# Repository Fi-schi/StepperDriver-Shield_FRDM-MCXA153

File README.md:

# StepperDriver-Shield_FRDM-MCXA153

This is a shield for the FRDM-MCXA153 microcontroller, developed as part of my mechatronic course project at the Hochschule Wismar, University of Applied Sciences: Technology, Economy and Design.

The board acts as a carrier for the TMC-2209 stepper drivers and allows up to four stepper motors to be controlled simultaneously.

It is designed for 24V operation and has three freely programmable buttons, connections for four limit switches and a manual stepper driver enable circuit.
In addition, by soldering a DC-DC converter to the microcontroller, it is possible to supply 24V through the shield.

# Parts for the shield

| Qty. | Part          | Size   | Links |
|------|:-------------:|:------:|:------|
|  7x  |     0.1µF     | 0805   |  |
|  4x  |    100µF/35V  | 6.3mm  | https://www.mouser.de/ProductDetail/661-EMZR350ARA101MF6 |
|  13x |    10K&Omega; | 0805   |  |
|  4x  |    100&Omega; | 0805   |  |
|  1x  |    1K&Omega;  | 0805   |  |
|  4x  |TVS-Diode 3.3V | 0603   | https://www.mouser.de/ProductDetail/652-CG0603MLC-3.3LE |
|  1x  |   74LVC2G00   |TSSOP-8 | https://www.mouser.de/ProductDetail/771-LVC2G00DP125 |
|  1x  |SN74LXC2T45-Q1 | 	VSSOP | https://www.mouser.de/ProductDetail/595-74LXC2T45QDCURQ1 |
|  1x  |    WS2812B    |        |  | 
|  5x  |Tactile Switch | 6x6mm  | https://www.mouser.de/ProductDetail/710-430133050816 |
|  4x  | 1x02 JST_XH   | 2,54mm |  |
|  4x  | 1x04 JST_XH   | 2,54mm |  |
|  1x  | 1x02 PinHeader| 2,54mm |  |
|  8x  | 1x03 PinHeader| 2,54mm |  |
|  9x  | Pin Header Jumper | 2,54mm |  |
|  1x  | AMASS XT60PW-M|        |  |
|  1x  | 2x06 PinHeader (SSW-106-23-G-D) | 2,54mm| https://www.samtec.com/de/products/ssw-106-23-g-d |
|  1x  | 2x08 PinHeader (SSW-108-23-G-D) | 2,54mm| https://www.samtec.com/de/products/ssw-108-23-g-d |
|  2x  | 3x10 PinHeader (SSW-110-23-G-D) | 2,54mm| https://www.samtec.com/de/products/ssw-110-23-g-d |
|  4x  | BTT TMC2019 Stepp Stick | |  |

# Parts for the microcontroller external power supply

| Qty. | Part          | Size   | Links |
|------|:-------------:|:------:|:------|
|  1x  | DC/DC to 5v/500mA| SIP-3  | https://www.mouser.de/ProductDetail/919-R-78CK5.0-0.5 |
|  2x  |    1µF/35V  | 0603  |  |

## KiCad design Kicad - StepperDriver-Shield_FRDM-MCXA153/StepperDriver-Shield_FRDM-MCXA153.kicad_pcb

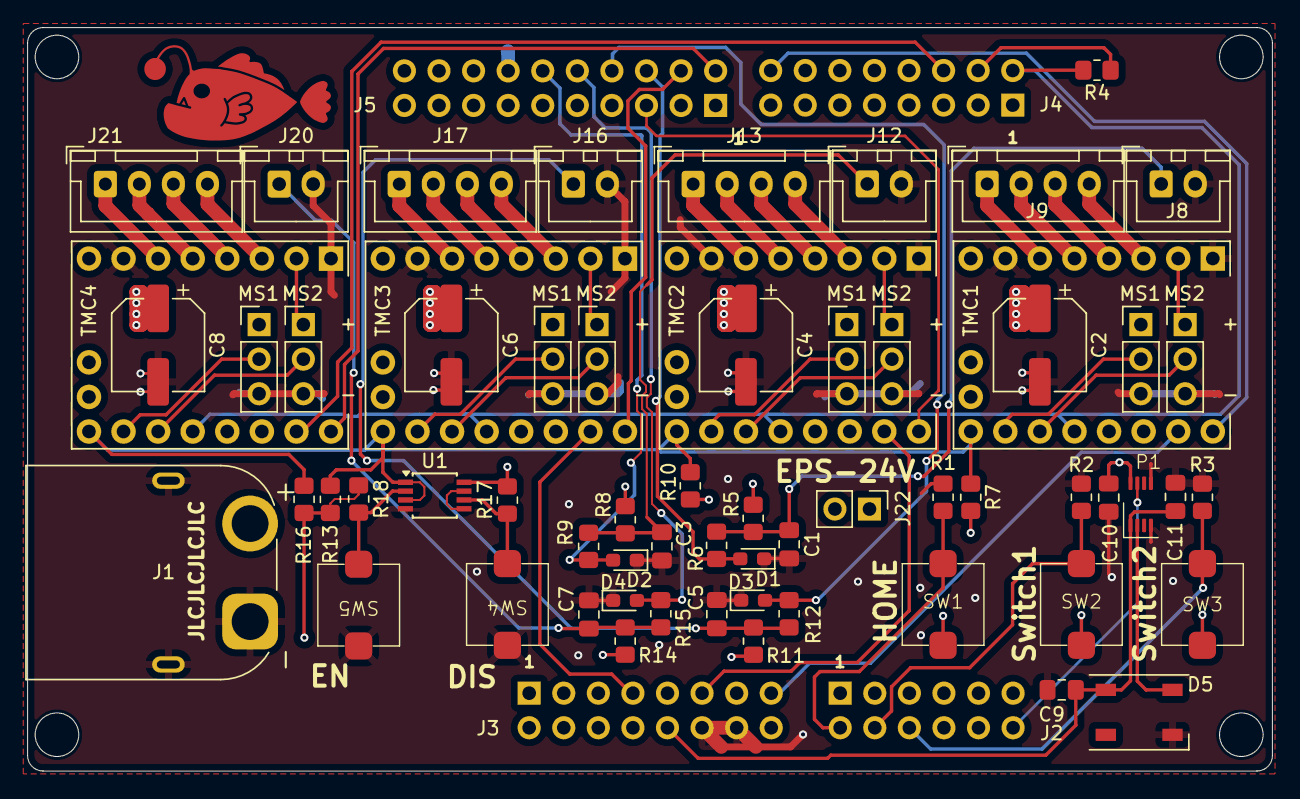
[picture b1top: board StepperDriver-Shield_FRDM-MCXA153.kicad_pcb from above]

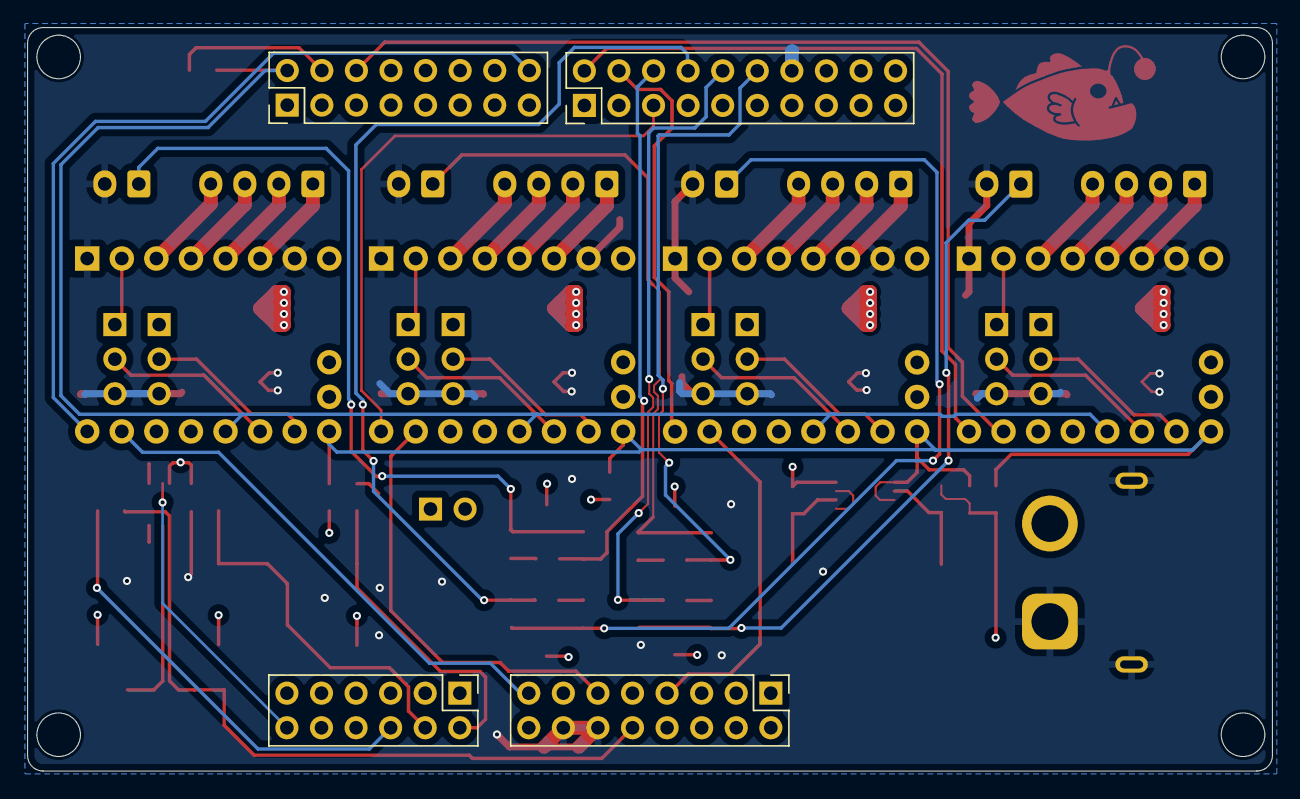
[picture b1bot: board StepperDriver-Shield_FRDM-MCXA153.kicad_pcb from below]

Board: 4 copper layers, 91.4 x 54.6 mm, 72 parts (4 on the bottom side), 56 nets.

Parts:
Blub1: Fischi
C1, C3, C5, C7: 0.1UF; C_0805_2012Metric_Pad1.18x1.45mm_HandSolder
C2, C4, C6, C8: 100UF/35V; CP_Elec_6.3x7.7
C9, C10, C11: 0.1µF; C_0805_2012Metric_Pad1.18x1.45mm_HandSolder
D1, D2, D3, D4: D_TVS; D_0603_1608Metric_Pad1.05x0.95mm_HandSolder
D5: WS2812B; LED_WS2812B_PLCC4_5.0x5.0mm_P3.2mm
H1, H2, H3, H4: Mechanical_MountingHole; MountingHole_3.2mm_M3
J1: Conn_01x02_Socket; AMASS_XT60PW-M
J2: SSQ-106-03-T-D; PinHeader_2x06_P2.54mm_Vertical
J3, J4: SSQ-108-03-T-D; PinHeader_2x08_P2.54mm_Vertical
J5: SSQ-110-03-T-D; PinHeader_2x10_P2.54mm_Vertical
J6, J7, J10, J11, J14, J15, J18, J19: Conn_01x03; PinHeader_1x03_P2.54mm_Vertical
J8, J12, J16, J20: Conn_01x02_Pin; JST_XH_B2B-XH-A_1x02_P2.50mm_Vertical
J9, J13, J17, J21: Conn_01x04_Pin; JST_XH_B4B-XH-A_1x04_P2.50mm_Vertical
J22: Conn_01x02_Socket; PinHeader_1x02_P2.54mm_Vertical
P1: SN74LXC2T45QDCURQ1_; SN74LXC2T45QDCURQ1
R1, R2, R3, R5, R7, R8, R10, R11, R13, R14, R16, R17, R18: 10K; R_0805_2012Metric_Pad1.20x1.40mm_HandSolder
R4: 1K; R_0805_2012Metric_Pad1.20x1.40mm_HandSolder
R6, R9, R12, R15: 100R; R_0805_2012Metric_Pad1.20x1.40mm_HandSolder
SW1: Home; Takt_Schalter_Aliexpress
SW2: SW1; Takt_Schalter_Aliexpress
SW3: SW2; Takt_Schalter_Aliexpress
SW4: DIS; Takt_Schalter_Aliexpress
SW5: EN; Takt_Schalter_Aliexpress
TMC1, TMC2, TMC3, TMC4: TMC2209; Btt_TMC2209_V1.3
U1: 74LVC2G00; TSSOP-8_3x3mm_P0.65mm

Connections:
5v-9v: J3.16, J22.1
/EN_Logic/ENABLE: U1.5, U1.7
/P1-4/UART2-RXD: J4.2, R4.2, TMC1.14 (RX), TMC2.14 (RX), TMC3.14 (RX), TMC4.14 (RX)
/P1-5/UART2-TXD: J4.4, R4.1
/P1-10/ADC0-A8: J2.2, R1.1, SW1.1
/P1-12/ADC0-A10: J2.4, R2.1, SW2.1
/P1-13/ADC0-A11: J2.6, R3.1, SW3.1
/P2-3/ADC0-A2: J5.5, TMC2.18 (DIR)
/P2-4/GPIO: J4.6, TMC4.17 (STEP)
/P2-6/CSI1: D1.2 (A2), J5.6, R6.2
/P2-12/SCK1: D2.2 (A2), J5.12, R9.2
/P2-13/SDO1: D3.2 (A2), J5.8, R12.2
/P2-16/SDI1: D4.2 (A2), J5.10, R15.2
/P3-1/GPIO: J4.16, TMC1.18 (DIR)
/P3-6/PWM0-A0: J3.15, TMC1.17 (STEP)
/P3-8/PWM0-A1: J3.11, TMC2.17 (STEP)
/P3-10/PWM0-A2: J3.7, TMC3.17 (STEP)
/P3-14/PWM0-X2: J5.4, TMC3.18 (DIR)
/P3-15/GPIO: J5.2, TMC4.18 (DIR)
/P3-30/ADC0-A13: J2.12, P1.7 (B1)
/TMC_2209_wiring1/A1: J13.2, TMC2.5 (A1)
/TMC_2209_wiring1/A2: J13.1, TMC2.6 (A2)
/TMC_2209_wiring1/B1: J13.3, TMC2.4 (B1)
/TMC_2209_wiring1/B2: J13.4, TMC2.3 (B2)
/TMC_2209_wiring1/MS1: J11.2, TMC2.12 (MS1)
/TMC_2209_wiring1/MS2: J10.2, TMC2.13 (MS2)
/TMC_2209_wiring2/A1: J17.2, TMC3.5 (A1)
/TMC_2209_wiring2/A2: J17.1, TMC3.6 (A2)
/TMC_2209_wiring2/B1: J17.3, TMC3.4 (B1)
/TMC_2209_wiring2/B2: J17.4, TMC3.3 (B2)
/TMC_2209_wiring2/MS1: J15.2, TMC3.12 (MS1)
/TMC_2209_wiring2/MS2: J14.2, TMC3.13 (MS2)
/TMC_2209_wiring3/A1: J21.2, TMC4.5 (A1)
/TMC_2209_wiring3/A2: J21.1, TMC4.6 (A2)
/TMC_2209_wiring3/B1: J21.3, TMC4.4 (B1)
/TMC_2209_wiring3/B2: J21.4, TMC4.3 (B2)
/TMC_2209_wiring3/MS1: J19.2, TMC4.12 (MS1)
/TMC_2209_wiring3/MS2: J18.2, TMC4.13 (MS2)
/TMC_2209_wiring/A1: J9.2, TMC1.5 (A1)
/TMC_2209_wiring/A2: J9.1, TMC1.6 (A2)
/TMC_2209_wiring/B1: J9.3, TMC1.4 (B1)
/TMC_2209_wiring/B2: J9.4, TMC1.3 (B2)
/TMC_2209_wiring/MS1: J7.2, TMC1.12 (MS1)
/TMC_2209_wiring/MS2: J6.2, TMC1.13 (MS2)
//ENABLE: R7.1, R10.1, R13.1, R16.1, TMC1.11 (/EN), TMC2.11 (/EN), TMC3.11 (/EN), TMC4.11 (/EN), U1.1, U1.3
GND: C1.2, C2.2, C3.2, C4.2, C5.2, C6.2, C7.2, C8.2, C9.1, C10.1, C11.2, D1.1 (A1), D2.1 (A1), D3.1 (A1), D4.1 (A1), D5.3 (VSS), J1.1, J3.12, J3.14, J5.14, J6.3, J7.3, J8.2, J10.3, J11.3, J12.2, J14.3, J15.3, J16.2, J18.3, J19.3, J20.2, P1.4 (GND), P1.5 (DIR), R1.2, R2.2, R3.2, SW4.1, SW5.1, TMC1.1 (GND), TMC1.7 (GND), TMC2.1 (GND), TMC2.7 (GND), TMC3.1 (GND), TMC3.7 (GND), TMC4.1 (GND), TMC4.7 (GND), U1.4 (GND)
unnamed: D5.4 (DIN), P1.2 (A1)
unnamed: C1.1, J8.1, R5.1, R6.1
unnamed: C3.1, J12.1, R8.1, R9.1
unnamed: C5.1, J16.1, R11.1, R12.1
unnamed: C7.1, J20.1, R14.1, R15.1
unnamed: R17.2, SW4.2, U1.6
unnamed: R18.2, SW5.2, U1.2
SYS-5V: C9.2, C11.1, D5.1 (VDD), J3.10, P1.1 (VCC_A)
Vcc_Logic: C10.2, J3.8, J6.1, J7.1, J10.1, J11.1, J14.1, J15.1, J18.1, J19.1, P1.8 (VCC_B), R5.2, R7.2, R8.2, R10.2, R11.2, R13.2, R14.2, R16.2, R17.1, R18.1, SW1.2, SW2.2, SW3.2, TMC1.2 (V_IO), TMC2.2 (V_IO), TMC3.2 (V_IO), TMC4.2 (V_IO), U1.8 (VCC)
Vcc_Motor: C2.1, C4.1, C6.1, C8.1, J1.2, J22.2, TMC1.8 (VS), TMC2.8 (VS), TMC3.8 (VS), TMC4.8 (VS)

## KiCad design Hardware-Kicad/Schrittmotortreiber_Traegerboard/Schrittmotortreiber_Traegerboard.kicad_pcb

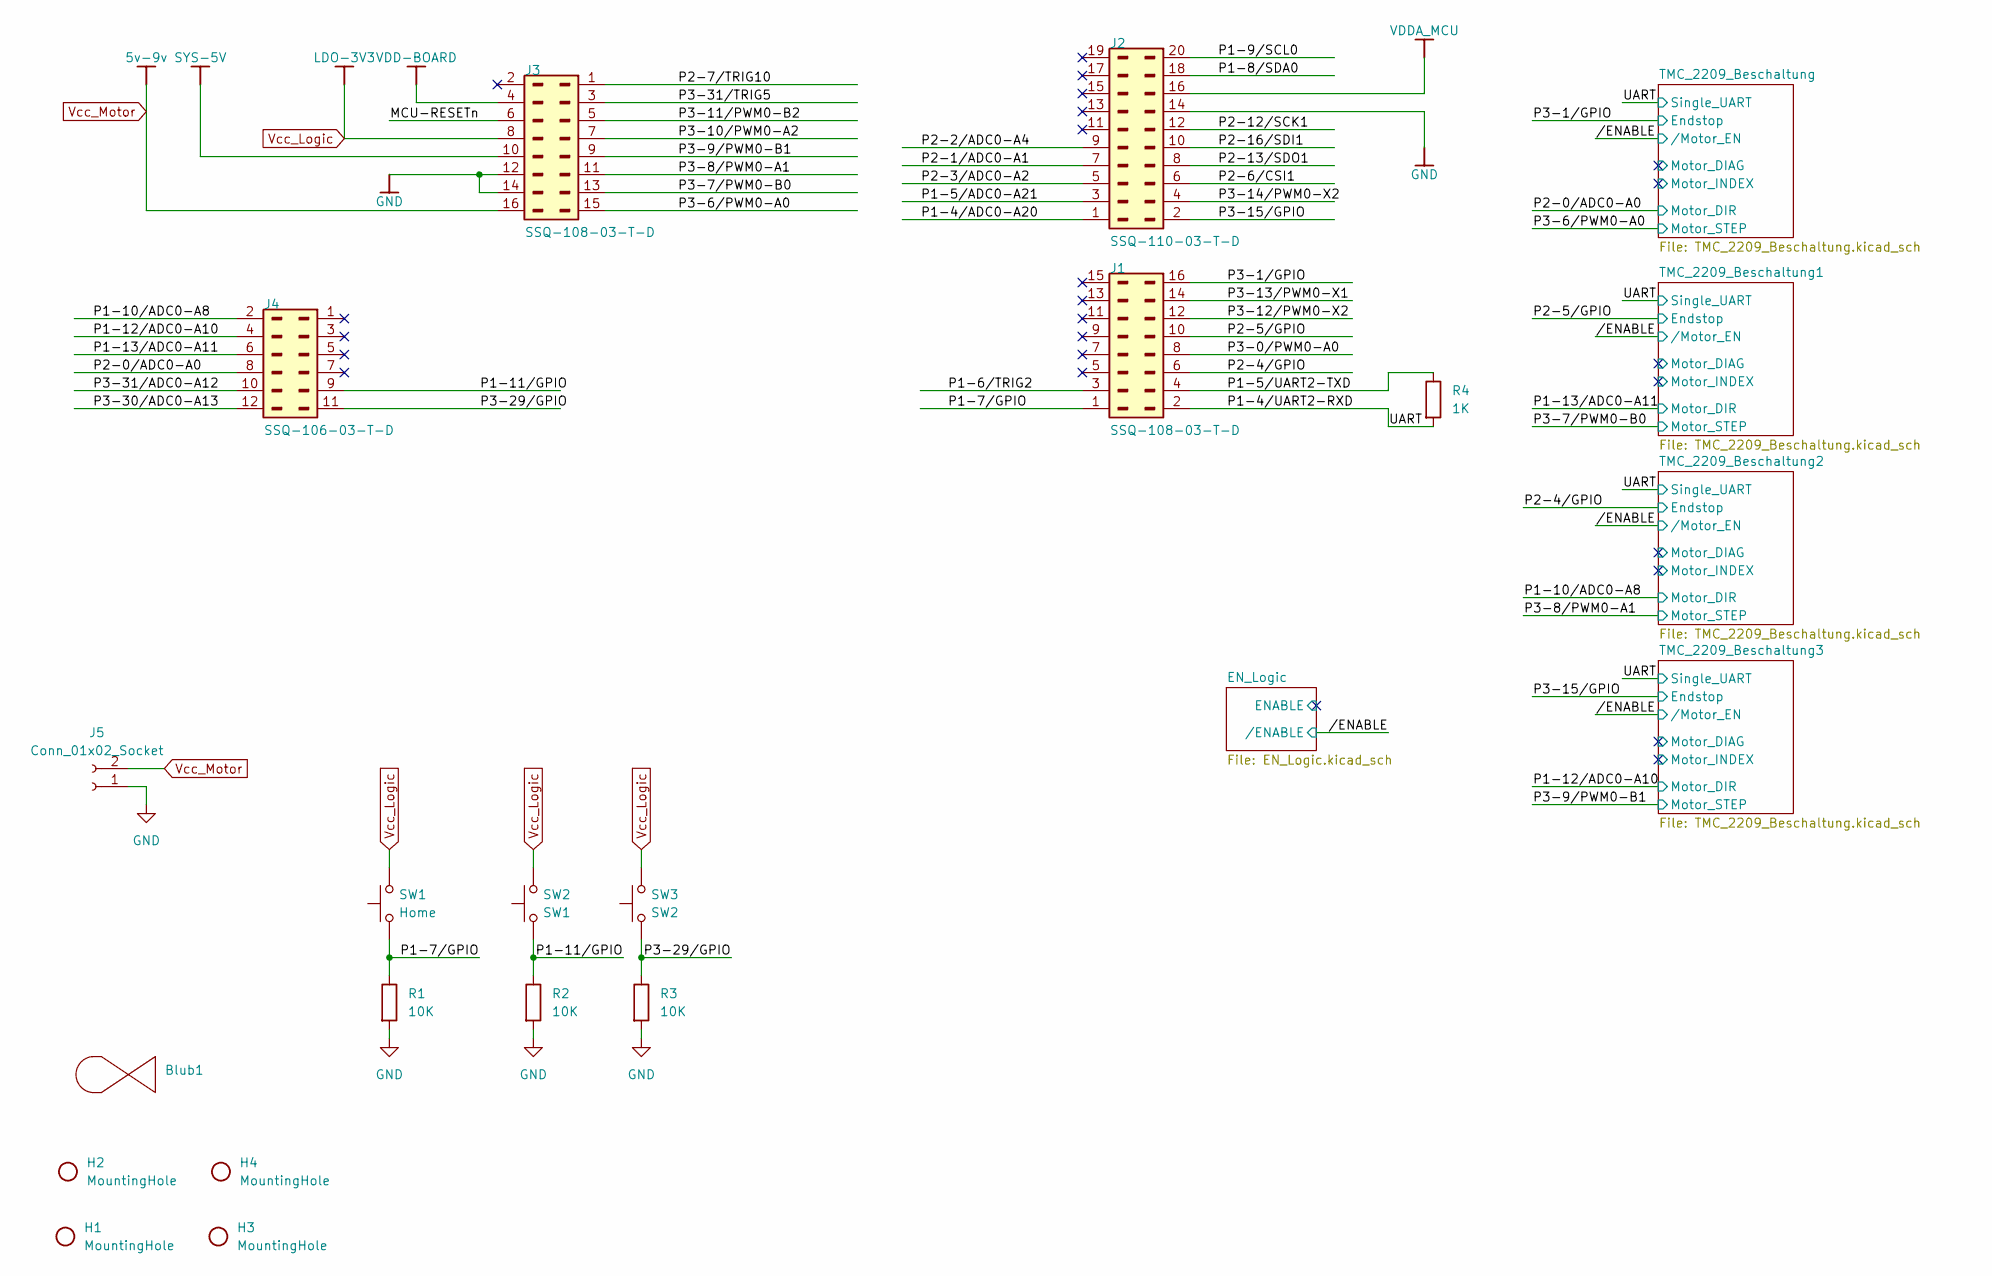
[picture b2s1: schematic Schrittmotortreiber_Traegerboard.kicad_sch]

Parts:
Blub1: Fischi
H1, H2, H3, H4: Mechanical_MountingHole; MountingHole_3.2mm_M3
J1, J3: SSQ-108-03-T-D; PinHeader_2x08_P2.54mm_Vertical; MANUFACTURER PART NUMBER SSQ-108-03-T-D
J2: SSQ-110-03-T-D; PinHeader_2x10_P2.54mm_Vertical; MANUFACTURER PART NUMBER SSQ-110-03-T-D
J4: SSQ-106-03-T-D; PinHeader_2x06_P2.54mm_Vertical; MANUFACTURER PART NUMBER SSQ-106-03-T-D
J5: Conn_01x02_Socket; AMASS_XT60PW-M
R1, R2, R3: 10K; R_0805_2012Metric_Pad1.20x1.40mm_HandSolder
R4: 1K; R_0805_2012Metric_Pad1.20x1.40mm_HandSolder
SW1: Home; Takt_Schalter_Aliexpress
SW2: SW1; Takt_Schalter_Aliexpress
SW3: SW2; Takt_Schalter_Aliexpress

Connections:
/MCU-RESETn: J3.6
/P1-4/ADC0-A20: J2.1
/P1-4/UART2-RXD: J1.2, R4.2; also elsewhere on the board
/P1-5/ADC0-A21: J2.3
/P1-5/UART2-TXD: J1.4, R4.1
/P1-6/TRIG2: J1.3
/P1-7/GPIO: J1.1, R1.1, SW1.1
/P1-8/SDA0: J2.18
/P1-9/SCL0: J2.20
/P1-10/ADC0-A8: J4.2; also elsewhere on the board
/P1-11/GPIO: J4.9, R2.1, SW2.1
/P1-12/ADC0-A10: J4.4; also elsewhere on the board
/P1-13/ADC0-A11: J4.6; also elsewhere on the board
/P2-0/ADC0-A0: J4.8; also elsewhere on the board
/P2-1/ADC0-A1: J2.7
/P2-2/ADC0-A4: J2.9
/P2-3/ADC0-A2: J2.5
/P2-4/GPIO: J1.6; also elsewhere on the board
/P2-5/GPIO: J1.10; also elsewhere on the board
/P2-6/CSI1: J2.6
/P2-7/TRIG10: J3.1
/P2-12/SCK1: J2.12
/P2-13/SDO1: J2.8
/P2-16/SDI1: J2.10
/P3-0/PWM0-A0: J1.8
/P3-1/GPIO: J1.16; also elsewhere on the board
/P3-6/PWM0-A0: J3.15; also elsewhere on the board
/P3-7/PWM0-B0: J3.13; also elsewhere on the board
/P3-8/PWM0-A1: J3.11; also elsewhere on the board
/P3-9/PWM0-B1: J3.9; also elsewhere on the board
/P3-10/PWM0-A2: J3.7
/P3-11/PWM0-B2: J3.5
/P3-12/PWM0-X2: J1.12
/P3-13/PWM0-X1: J1.14
/P3-14/PWM0-X2: J2.4
/P3-15/GPIO: J2.2; also elsewhere on the board
/P3-29/GPIO: J4.11, R3.1, SW3.1
/P3-30/ADC0-A13: J4.12
/P3-31/ADC0-A12: J4.10
/P3-31/TRIG5: J3.3
GND: J2.14, J3.12, J3.14, J5.1, R1.2, R2.2, R3.2; also elsewhere on the board
SYS-5V: J3.10
VDD-BOARD: J3.4
VDDA_MCU: J2.16
Vcc_Logic: J3.8, SW1.2, SW2.2, SW3.2; also elsewhere on the board
Vcc_Motor: J3.16, J5.2; also elsewhere on the board

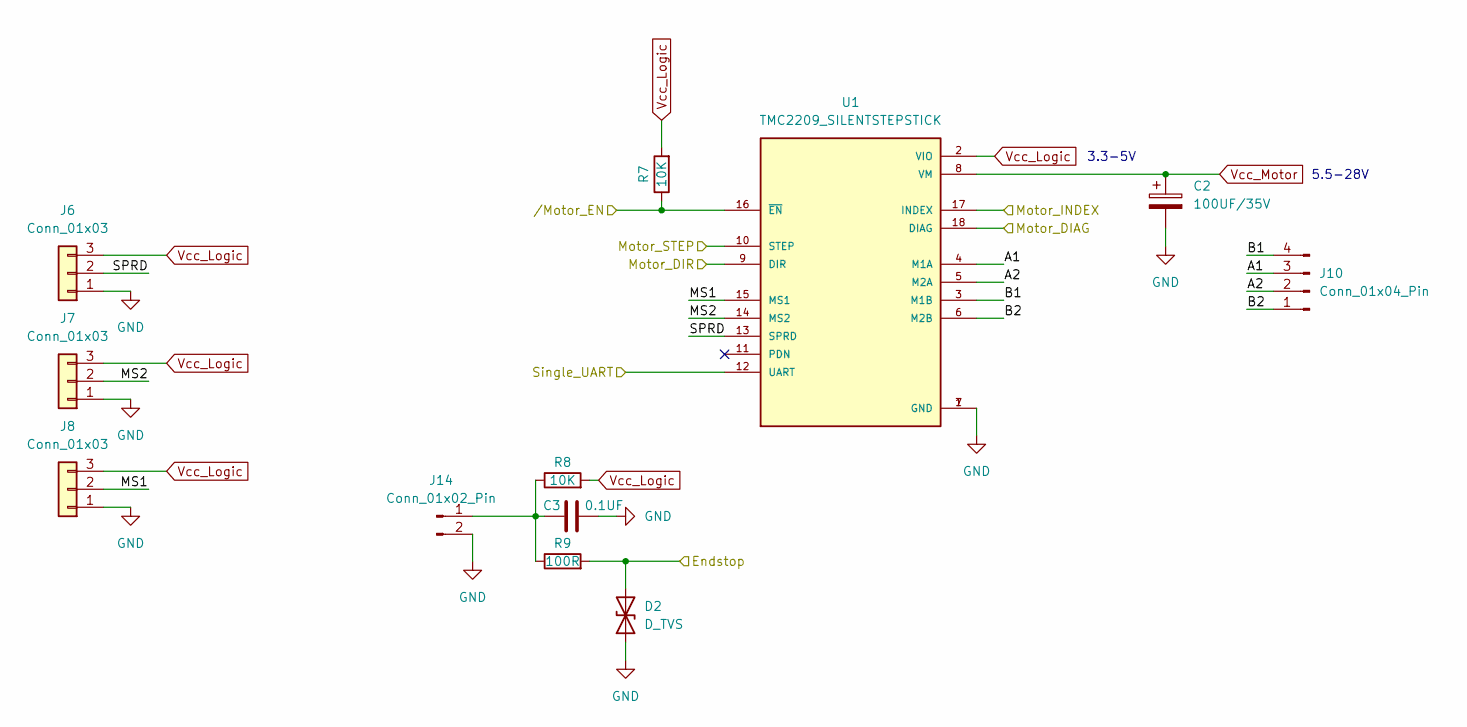
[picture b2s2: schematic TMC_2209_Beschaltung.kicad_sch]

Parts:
C2: 100UF/35V; CP_Elec_6.3x7.7
C3: 0.1UF; C_0805_2012Metric_Pad1.18x1.45mm_HandSolder
D2: D_TVS; D_0201_0603Metric_Pad0.64x0.40mm_HandSolder
J6, J7, J8: Conn_01x03; PinHeader_1x03_P2.54mm_Vertical
J10: Conn_01x04_Pin; JST_XH_B4B-XH-A_1x04_P2.50mm_Vertical
J14: Conn_01x02_Pin; JST_XH_B2B-XH-A_1x02_P2.50mm_Vertical
R7, R8: 10K; R_0805_2012Metric_Pad1.20x1.40mm_HandSolder
R9: 100R; R_0805_2012Metric_Pad1.20x1.40mm_HandSolder
U1: TMC2209_SILENTSTEPSTICK; MODULE_TMC2209_SILENTSTEPSTICK; PARTREV 1.20

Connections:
/P1-4/UART2-RXD: U1.12 (UART); also elsewhere on the board
/P2-0/ADC0-A0: U1.9 (DIR); also elsewhere on the board
/P2-5/GPIO: D2.2 (A2), R9.2; also elsewhere on the board
/P3-6/PWM0-A0: U1.10 (STEP); also elsewhere on the board
/TMC_2209_Beschaltung/A1: J10.3, U1.4 (M1A)
/TMC_2209_Beschaltung/A2: J10.2, U1.5 (M2A)
/TMC_2209_Beschaltung/B1: J10.4, U1.3 (M1B)
/TMC_2209_Beschaltung/B2: J10.1, U1.6 (M2B)
/TMC_2209_Beschaltung/MS1: J8.2, U1.15 (MS1)
/TMC_2209_Beschaltung/MS2: J7.2, U1.14 (MS2)
/TMC_2209_Beschaltung/Motor_DIAG: U1.18 (DIAG)
/TMC_2209_Beschaltung/Motor_INDEX: U1.17 (INDEX)
/TMC_2209_Beschaltung/SPRD: J6.2, U1.13 (SPRD)
//ENABLE: R7.1, U1.16 (~EN); also elsewhere on the board
GND: C2.2, C3.2, D2.1 (A1), J6.1, J7.1, J8.1, J14.2, U1.1 (GND), U1.7 (GND); also elsewhere on the board
unnamed: C3.1, J14.1, R8.1, R9.1
Vcc_Logic: J6.3, J7.3, J8.3, R7.2, R8.2, U1.2 (VIO); also elsewhere on the board
Vcc_Motor: C2.1, U1.8 (VM); also elsewhere on the board

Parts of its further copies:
C1, C5, C7: 0.1UF; C_0805_2012Metric_Pad1.18x1.45mm_HandSolder
C4, C6, C8: 100UF/35V; CP_Elec_6.3x7.7
D1, D3, D4: D_TVS; D_0201_0603Metric_Pad0.64x0.40mm_HandSolder
J9, J19, J24: Conn_01x02_Pin; JST_XH_B2B-XH-A_1x02_P2.50mm_Vertical
J11, J12, J13, J16, J17, J18, J21, J22, J23: Conn_01x03; PinHeader_1x03_P2.54mm_Vertical
J15, J20, J25: Conn_01x04_Pin; JST_XH_B4B-XH-A_1x04_P2.50mm_Vertical
R5, R10, R11, R13, R14, R16: 10K; R_0805_2012Metric_Pad1.20x1.40mm_HandSolder
R6, R12, R15: 100R; R_0805_2012Metric_Pad1.20x1.40mm_HandSolder
U2, U3, U4: TMC2209_SILENTSTEPSTICK; MODULE_TMC2209_SILENTSTEPSTICK; PARTREV 1.20

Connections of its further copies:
/P1-4/UART2-RXD: U2.12 (UART), U3.12 (UART), U4.12 (UART); also elsewhere on the board
/P1-10/ADC0-A8: U3.9 (DIR); also elsewhere on the board
/P1-12/ADC0-A10: U4.9 (DIR); also elsewhere on the board
/P1-13/ADC0-A11: U2.9 (DIR); also elsewhere on the board
/P2-4/GPIO: D3.2 (A2), R12.2; also elsewhere on the board
/P3-1/GPIO: D1.2 (A2), R6.2; also elsewhere on the board
/P3-7/PWM0-B0: U2.10 (STEP); also elsewhere on the board
/P3-8/PWM0-A1: U3.10 (STEP); also elsewhere on the board
/P3-9/PWM0-B1: U4.10 (STEP); also elsewhere on the board
/P3-15/GPIO: D4.2 (A2), R15.2; also elsewhere on the board
/TMC_2209_Beschaltung1/A1: J15.3, U2.4 (M1A)
/TMC_2209_Beschaltung1/A2: J15.2, U2.5 (M2A)
/TMC_2209_Beschaltung1/B1: J15.4, U2.3 (M1B)
/TMC_2209_Beschaltung1/B2: J15.1, U2.6 (M2B)
/TMC_2209_Beschaltung1/MS1: J13.2, U2.15 (MS1)
/TMC_2209_Beschaltung1/MS2: J12.2, U2.14 (MS2)
/TMC_2209_Beschaltung1/Motor_DIAG: U2.18 (DIAG)
/TMC_2209_Beschaltung1/Motor_INDEX: U2.17 (INDEX)
/TMC_2209_Beschaltung1/SPRD: J11.2, U2.13 (SPRD)
/TMC_2209_Beschaltung2/A1: J20.3, U3.4 (M1A)
/TMC_2209_Beschaltung2/A2: J20.2, U3.5 (M2A)
/TMC_2209_Beschaltung2/B1: J20.4, U3.3 (M1B)
/TMC_2209_Beschaltung2/B2: J20.1, U3.6 (M2B)
/TMC_2209_Beschaltung2/MS1: J18.2, U3.15 (MS1)
/TMC_2209_Beschaltung2/MS2: J17.2, U3.14 (MS2)
/TMC_2209_Beschaltung2/Motor_DIAG: U3.18 (DIAG)
/TMC_2209_Beschaltung2/Motor_INDEX: U3.17 (INDEX)
/TMC_2209_Beschaltung2/SPRD: J16.2, U3.13 (SPRD)
/TMC_2209_Beschaltung3/A1: J25.3, U4.4 (M1A)
/TMC_2209_Beschaltung3/A2: J25.2, U4.5 (M2A)
/TMC_2209_Beschaltung3/B1: J25.4, U4.3 (M1B)
/TMC_2209_Beschaltung3/B2: J25.1, U4.6 (M2B)
/TMC_2209_Beschaltung3/MS1: J23.2, U4.15 (MS1)
/TMC_2209_Beschaltung3/MS2: J22.2, U4.14 (MS2)
/TMC_2209_Beschaltung3/Motor_DIAG: U4.18 (DIAG)
/TMC_2209_Beschaltung3/Motor_INDEX: U4.17 (INDEX)
/TMC_2209_Beschaltung3/SPRD: J21.2, U4.13 (SPRD)
//ENABLE: R10.1, R13.1, R16.1, U2.16 (~EN), U3.16 (~EN), U4.16 (~EN); also elsewhere on the board
GND: C1.2, C4.2, C5.2, C6.2, C7.2, C8.2, D1.1 (A1), D3.1 (A1), D4.1 (A1), J9.2, J11.1, J12.1, J13.1, J16.1, J17.1, J18.1, J19.2, J21.1, J22.1, J23.1, J24.2, U2.1 (GND), U2.7 (GND), U3.1 (GND), U3.7 (GND), U4.1 (GND), U4.7 (GND); also elsewhere on the board
unnamed: C1.1, J9.1, R5.1, R6.1
unnamed: C5.1, J19.1, R11.1, R12.1
unnamed: C7.1, J24.1, R14.1, R15.1
Vcc_Logic: J11.3, J12.3, J13.3, J16.3, J17.3, J18.3, J21.3, J22.3, J23.3, R5.2, R10.2, R11.2, R13.2, R14.2, R16.2, U2.2 (VIO), U3.2 (VIO), U4.2 (VIO); also elsewhere on the board
Vcc_Motor: C4.1, C6.1, C8.1, U2.8 (VM), U3.8 (VM), U4.8 (VM); also elsewhere on the board

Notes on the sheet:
5.5-28V
3.3-5V

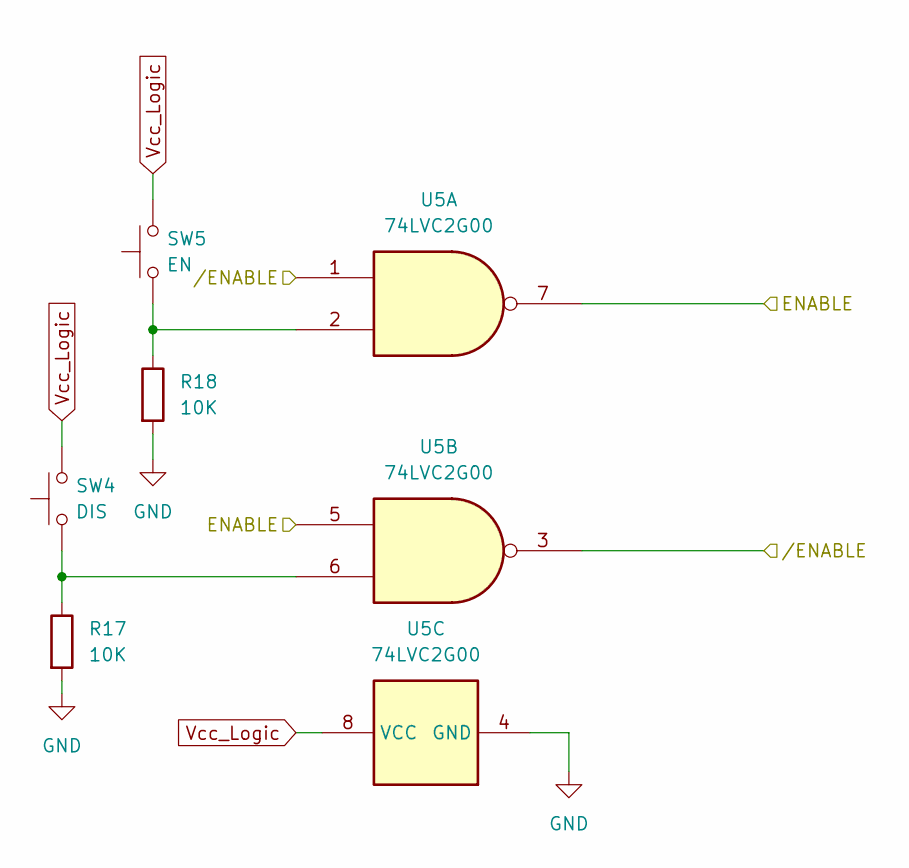
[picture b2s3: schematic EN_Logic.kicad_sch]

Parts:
R17, R18: 10K; R_0805_2012Metric_Pad1.20x1.40mm_HandSolder
SW4: DIS; Takt_Schalter_Aliexpress
SW5: EN; Takt_Schalter_Aliexpress
U5: 74LVC2G00; TSSOP-8_3x3mm_P0.65mm

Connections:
/EN_Logic/ENABLE: U5.5, U5.7
//ENABLE: U5.1, U5.3; also elsewhere on the board
GND: R17.2, R18.2, U5.4 (GND); also elsewhere on the board
unnamed: R17.1, SW4.1, U5.6
unnamed: R18.1, SW5.1, U5.2
Vcc_Logic: SW4.2, SW5.2, U5.8 (VCC); also elsewhere on the board

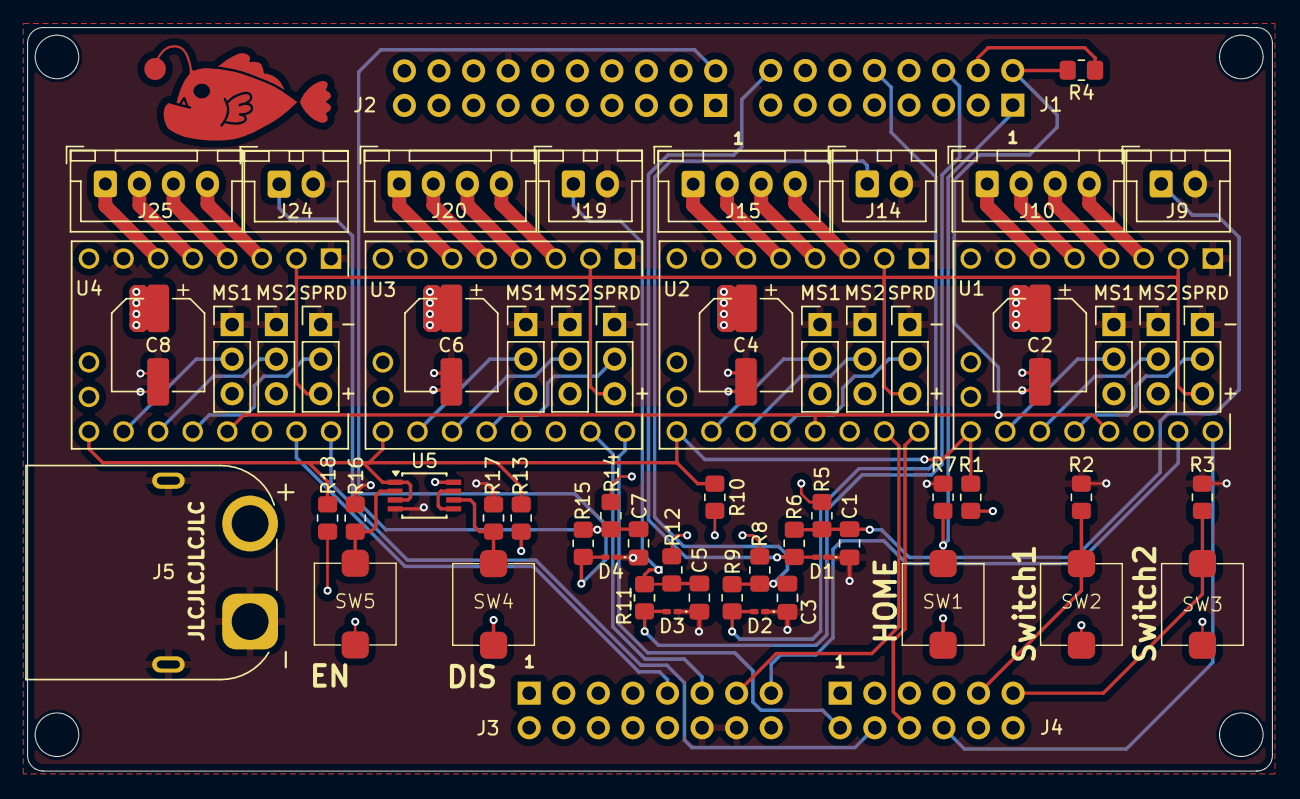
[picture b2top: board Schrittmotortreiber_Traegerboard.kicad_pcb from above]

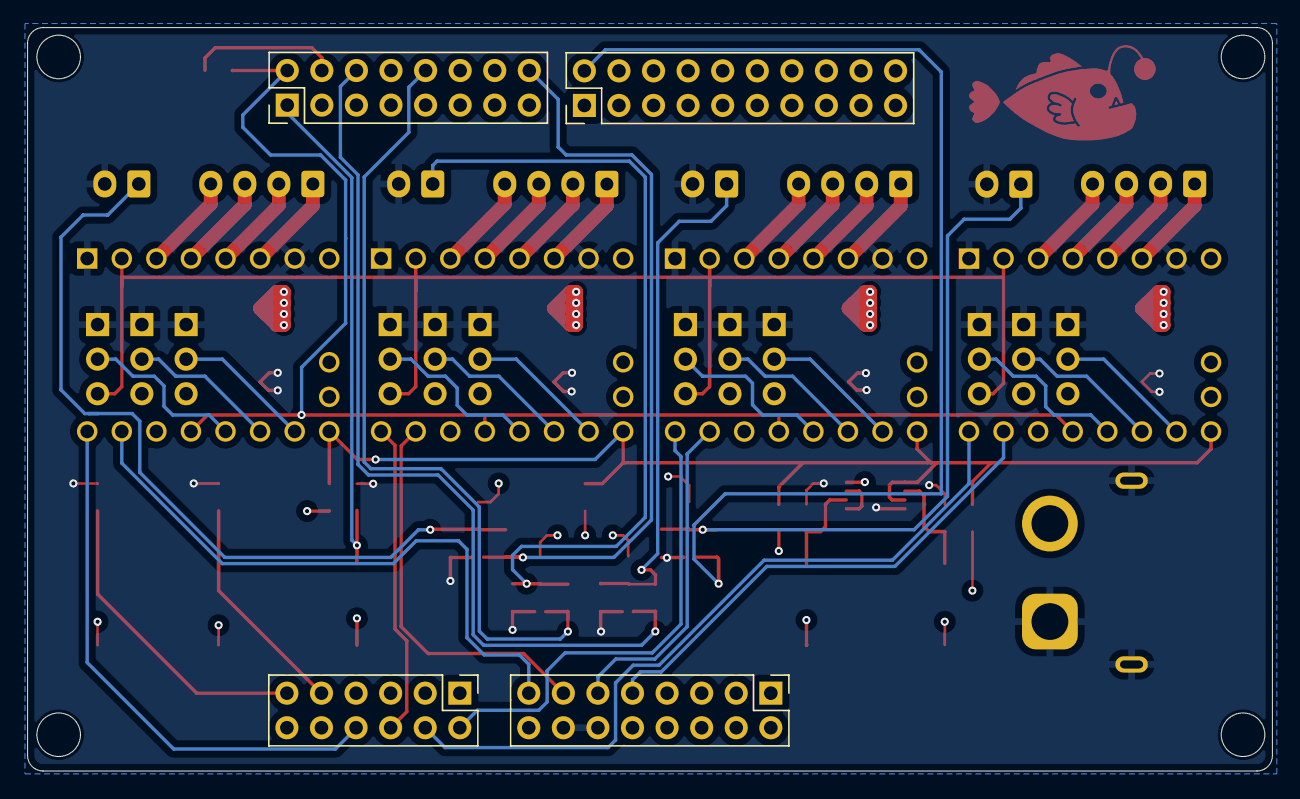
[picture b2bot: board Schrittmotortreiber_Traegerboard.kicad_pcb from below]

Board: 4 copper layers, 91.4 x 54.6 mm, 70 parts (4 on the bottom side), 56 nets.

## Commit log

2024-04-26 first push
2024-04-26 test
2024-06-29 New Revision
2024-06-29 Update 3D Models
2024-06-29 Renaming
2024-06-29 Resizing pictures
2024-06-30 Update README.md
    Add Partlist
2024-06-30 Update gerber to order
2024-07-06 Added Status RGB LED
2024-07-06 Update Gerber Files
